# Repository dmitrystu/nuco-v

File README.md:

# NUCO-V

+ Designed for the STM32F7 and STM32H7 series
+ Pin-compatible with NUCLEO-64 boards
+ Integrated [Blackmagic probe](https://github.com/blacksphere/blackmagic)

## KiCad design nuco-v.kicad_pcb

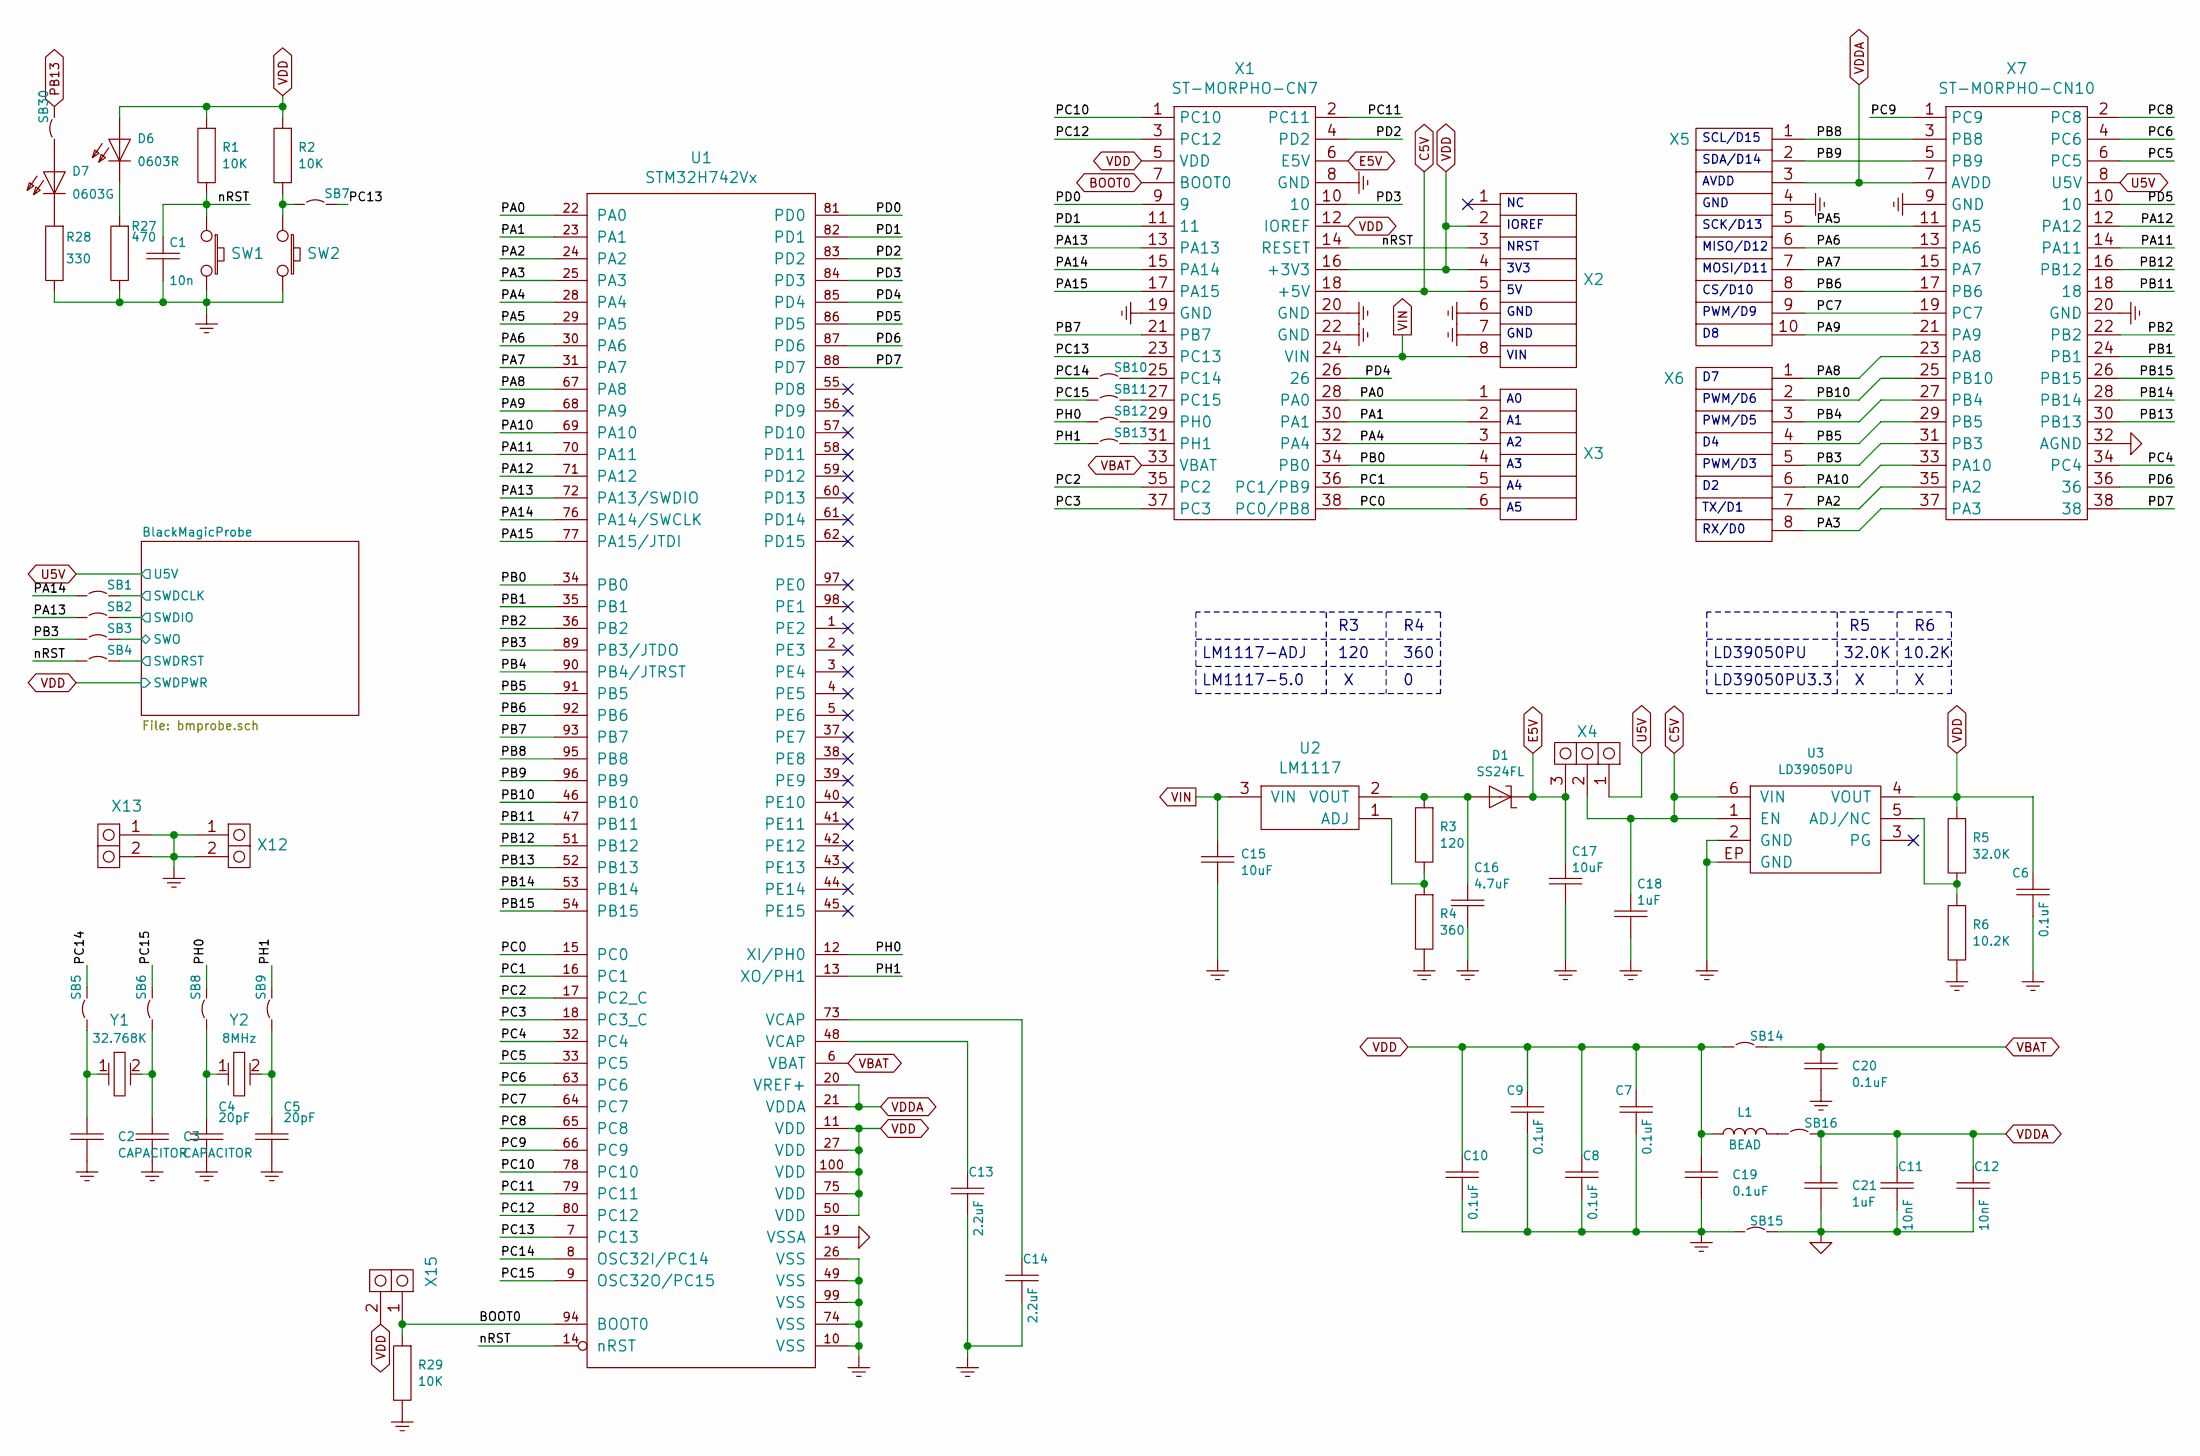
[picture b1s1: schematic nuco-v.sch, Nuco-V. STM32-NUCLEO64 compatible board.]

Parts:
C1: 10n; SMD-0603C
C2, C3: CAPACITOR; SMD-0603C
C4, C5: 20pF; SMD-0603C
C6, C7, C8, C9, C10, C19, C20: 0.1uF; SMD-0603C
C11, C12: 10nF; SMD-0603C
C13, C14: 2.2uF; SMD-0603C
C15, C17: 10uF; SMD-1206C
C16: 4.7uF; SMD-0805C
C18, C21: 1uF; SMD-0603C
D1: SS24FL; SOD-123F
D6: 0603R; LED-0603
D7: 0603G; LED-0603
L1: BEAD; SMD-0603L
R1, R2, R29: 10K; SMD-0603R
R3: 120; SMD-0603R
R4: 360; SMD-0603R
R5: 32.0K; SMD-0603R
R6: 10.2K; SMD-0603R
R27: 470; SMD-0603R
R28: 330; SMD-0603R
SB1, SB2, SB3, SB4, SB5, SB6, SB7, SB8, SB9, SB10, SB11, SB12, SB13, SB14, SB15, SB16, SB30: JUMPER; SMD-0603R
SW1, SW2: BUTTON1; B3U-1000P-B
U1: STM32H742Vx; QFPX50P140X140-100
U2: LM1117; SOT-223-3
U3: LD39050PU; DFNX95P030X030-6
X1: ST-MORPHO-CN7; DS1021-2X19S61
X2: CONN-08P1L; DS1023-1X08A
X3: CONN-06P1L; DS1025-1X06S61
X4: CONN-03P1L; DS1021-1X03S61
X5: CONN-10P1L; DS1023-1X10A
X6: CONN-08P1L; DS1021-2X04S61
X7: ST-MORPHO-CN10; DS1021-2X19S61
X12, X13: CONN-02P1LA; DS1021-1X02S61
X15: CONN-02P1L; DS1021-1X02S61
Y1: 32.768K; KX-327L
Y2: 8MHz; KX-3H

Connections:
/BlackMagicProbe/SWDCLK: SB1.2 (J2); also elsewhere on the board
/BlackMagicProbe/SWDIO: SB2.2 (J2); also elsewhere on the board
/BlackMagicProbe/SWDRST: SB4.2 (J2); also elsewhere on the board
/BlackMagicProbe/SWO: SB3.2 (J2); also elsewhere on the board
/PA0: U1.22 (PA0), X1.28 (PA0), X3.1
/PA1: U1.23 (PA1), X1.30 (PA1), X3.2
/PA2: U1.24 (PA2), X6.7, X7.35 (PA2)
/PA3: U1.25 (PA3), X6.8, X7.37 (PA3)
/PA4: U1.28 (PA4), X1.32 (PA4), X3.3
/PA5: U1.29 (PA5), X5.5, X7.11 (PA5)
/PA6: U1.30 (PA6), X5.6, X7.13 (PA6)
/PA7: U1.31 (PA7), X5.7, X7.15 (PA7)
/PA8: U1.67 (PA8), X6.1, X7.23 (PA8)
/PA9: U1.68 (PA9), X5.10, X7.21 (PA9)
/PA10: U1.69 (PA10), X6.6, X7.33 (PA10)
/PA11: U1.70 (PA11), X7.14 (PA11)
/PA12: U1.71 (PA12), X7.12 (PA12)
/PA13: SB2.1 (J1), U1.72 (PA13/SWDIO), X1.13 (PA13)
/PA14: SB1.1 (J1), U1.76 (PA14/SWCLK), X1.15 (PA14)
/PA15: U1.77 (PA15/JTDI), X1.17 (PA15)
/PB0: U1.34 (PB0), X1.34 (PB0), X3.4
/PB1: U1.35 (PB1), X7.24 (PB1)
/PB2: U1.36 (PB2), X7.22 (PB2)
/PB3: SB3.1 (J1), U1.89 (PB3/JTDO), X6.5, X7.31 (PB3)
/PB4: U1.90 (PB4/JTRST), X6.3, X7.27 (PB4)
/PB5: U1.91 (PB5), X6.4, X7.29 (PB5)
/PB6: U1.92 (PB6), X5.8, X7.17 (PB6)
/PB7: U1.93 (PB7), X1.21 (PB7)
/PB8: U1.95 (PB8), X5.1, X7.3 (PB8)
/PB9: U1.96 (PB9), X5.2, X7.5 (PB9)
/PB10: U1.46 (PB10), X6.2, X7.25 (PB10)
/PB11: U1.47 (PB11), X7.18
/PB12: U1.51 (PB12), X7.16 (PB12)
/PB14: U1.53 (PB14), X7.28 (PB14)
/PB15: U1.54 (PB15), X7.26 (PB15)
/PC0: U1.15 (PC0), X1.38 (PC0/PB8), X3.6
/PC1: U1.16 (PC1), X1.36 (PC1/PB9), X3.5
/PC2: U1.17 (PC2_C), X1.35 (PC2)
/PC3: U1.18 (PC3_C), X1.37 (PC3)
/PC4: U1.32 (PC4), X7.34 (PC4)
/PC5: U1.33 (PC5), X7.6 (PC5)
/PC6: U1.63 (PC6), X7.4 (PC6)
/PC7: U1.64 (PC7), X5.9, X7.19 (PC7)
/PC8: U1.65 (PC8), X7.2 (PC8)
/PC9: U1.66 (PC9), X7.1 (PC9)
/PC10: U1.78 (PC10), X1.1 (PC10)
/PC11: U1.79 (PC11), X1.2 (PC11)
/PC12: U1.80 (PC12), X1.3 (PC12)
/PC13: SB7.2 (J2), U1.7 (PC13), X1.23 (PC13)
/PC14: SB5.2 (J2), SB10.1 (J1), U1.8 (OSC32I/PC14)
/PC15: SB6.2 (J2), SB11.1 (J1), U1.9 (OSC32O/PC15)
/PD0: U1.81 (PD0), X1.9
/PD1: U1.82 (PD1), X1.11
/PD2: U1.83 (PD2), X1.4 (PD2)
/PD3: U1.84 (PD3), X1.10
/PD4: U1.85 (PD4), X1.26
/PD5: U1.86 (PD5), X7.10
/PD6: U1.87 (PD6), X7.36
/PD7: U1.88 (PD7), X7.38
/PH0: SB8.2 (J2), SB12.1 (J1), U1.12 (XI/PH0)
/PH1: SB9.2 (J2), SB13.1 (J1), U1.13 (XO/PH1)
/nRST: C1.1 (C1), R1.2 (R2), SB4.1 (J1), SW1.1 (CMN), U1.14 (nRST), X1.14 (RESET), X2.3
AGND: C11.2 (C2), C12.2 (C2), C21.2 (C2), SB15.2 (J2), U1.19 (VSSA), X7.32 (AGND)
BOOT0: R29.1 (R1), U1.94 (BOOT0), X1.7 (BOOT0), X15.1
C5V: C18.1 (C1), U3.1 (EN), U3.6 (VIN), X1.18 (+5V), X2.5, X4.2
E5V: C17.1 (C1), D1.1 (K), X1.6 (E5V), X4.3
unnamed: C2.1 (C1), SB5.1 (J1), Y1.1 (Q1)
unnamed: C3.1 (C1), SB6.1 (J1), Y1.2 (Q2)
unnamed: C4.1 (C1), SB8.1 (J1), Y2.1 (Q1)
unnamed: C5.1 (C1), SB9.1 (J1), Y2.2 (Q2)
unnamed: C13.1 (C1), U1.48 (VCAP)
unnamed: C14.1 (C1), U1.73 (VCAP)
unnamed: C16.1 (C1), D1.2 (A), R3.1 (R1), U2.2 (VOUT)
unnamed: D6.K, R27.1 (R1)
unnamed: D7.A, SB30.1 (J1)
unnamed: D7.K, R28.1 (R1)
unnamed: L1.2 (R2), SB16.1 (J1)
unnamed: R2.2 (R2), SB7.1 (J1), SW2.1 (CMN)
unnamed: R3.2 (R2), R4.1 (R1), U2.1 (ADJ)
unnamed: R5.2 (R2), R6.1 (R1), U3.5 (ADJ/NC)
unnamed: SB10.2 (J2), X1.25 (PC14)
unnamed: SB11.2 (J2), X1.27 (PC15)
unnamed: SB12.2 (J2), X1.29 (PH0)
unnamed: SB13.2 (J2), X1.31 (PH1)
PB13: SB30.2 (J2), U1.52 (PB13), X7.30 (PB13)
PGND: C1.2 (C2), C2.2 (C2), C3.2 (C2), C4.2 (C2), C5.2 (C2), C6.2 (C2), C7.2 (C2), C8.2 (C2), C9.2 (C2), C10.2 (C2), C13.2 (C2), C14.2 (C2), C15.2 (C2), C16.2 (C2), C17.2 (C2), C18.2 (C2), C19.2 (C2), C20.2 (C2), R4.2 (R2), R6.2 (R2), R27.2 (R2), R28.2 (R2), R29.2 (R2), SB15.1 (J1), SW1.2 (NO), SW2.2 (NO), U1.10 (VSS), U1.26 (VSS), U1.49 (VSS), U1.74 (VSS), U1.99 (VSS), U3.2 (GND), U3.EP (GND), X1.8 (GND), X1.19 (GND), X1.20 (GND), X1.22 (GND), X2.6, X2.7, X5.4, X7.9 (GND), X7.20 (GND), X12.1, X12.2, X13.1, X13.2; also elsewhere on the board
U5V: X4.1, X7.8 (U5V); also elsewhere on the board
VBAT: C20.1 (C1), SB14.2 (J2), U1.6 (VBAT), X1.33 (VBAT)
VDD: C6.1 (C1), C7.1 (C1), C8.1 (C1), C9.1 (C1), C10.1 (C1), C19.1 (C1), D6.A, L1.1 (R1), R1.1 (R1), R2.1 (R1), R5.1 (R1), SB14.1 (J1), U1.11 (VDD), U1.27 (VDD), U1.50 (VDD), U1.75 (VDD), U1.100 (VDD), U3.4 (VOUT), X1.5 (VDD), X1.12 (IOREF), X1.16 (+3V3), X2.2, X2.4, X15.2; also elsewhere on the board
VDDA: C11.1 (C1), C12.1 (C1), C21.1 (C1), SB16.2 (J2), U1.20 (VREF+), U1.21 (VDDA), X5.3, X7.7 (AVDD)
VIN: C15.1 (C1), U2.3 (VIN), X1.24 (VIN), X2.8

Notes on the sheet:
SCL/D15
SDA/D14
AVDD
GND
SCK/D13
MISO/D12
MOSI/D11
CS/D10
PWM/D9
PWM/D6
PWM/D5
PWM/D3
TX/D1
RX/D0
IOREF
NRST
3V3
VIN
LM1117-ADJ
LM1117-5.0
120
360
LD39050PU
LD39050PU3.3
10.2K
32.0K

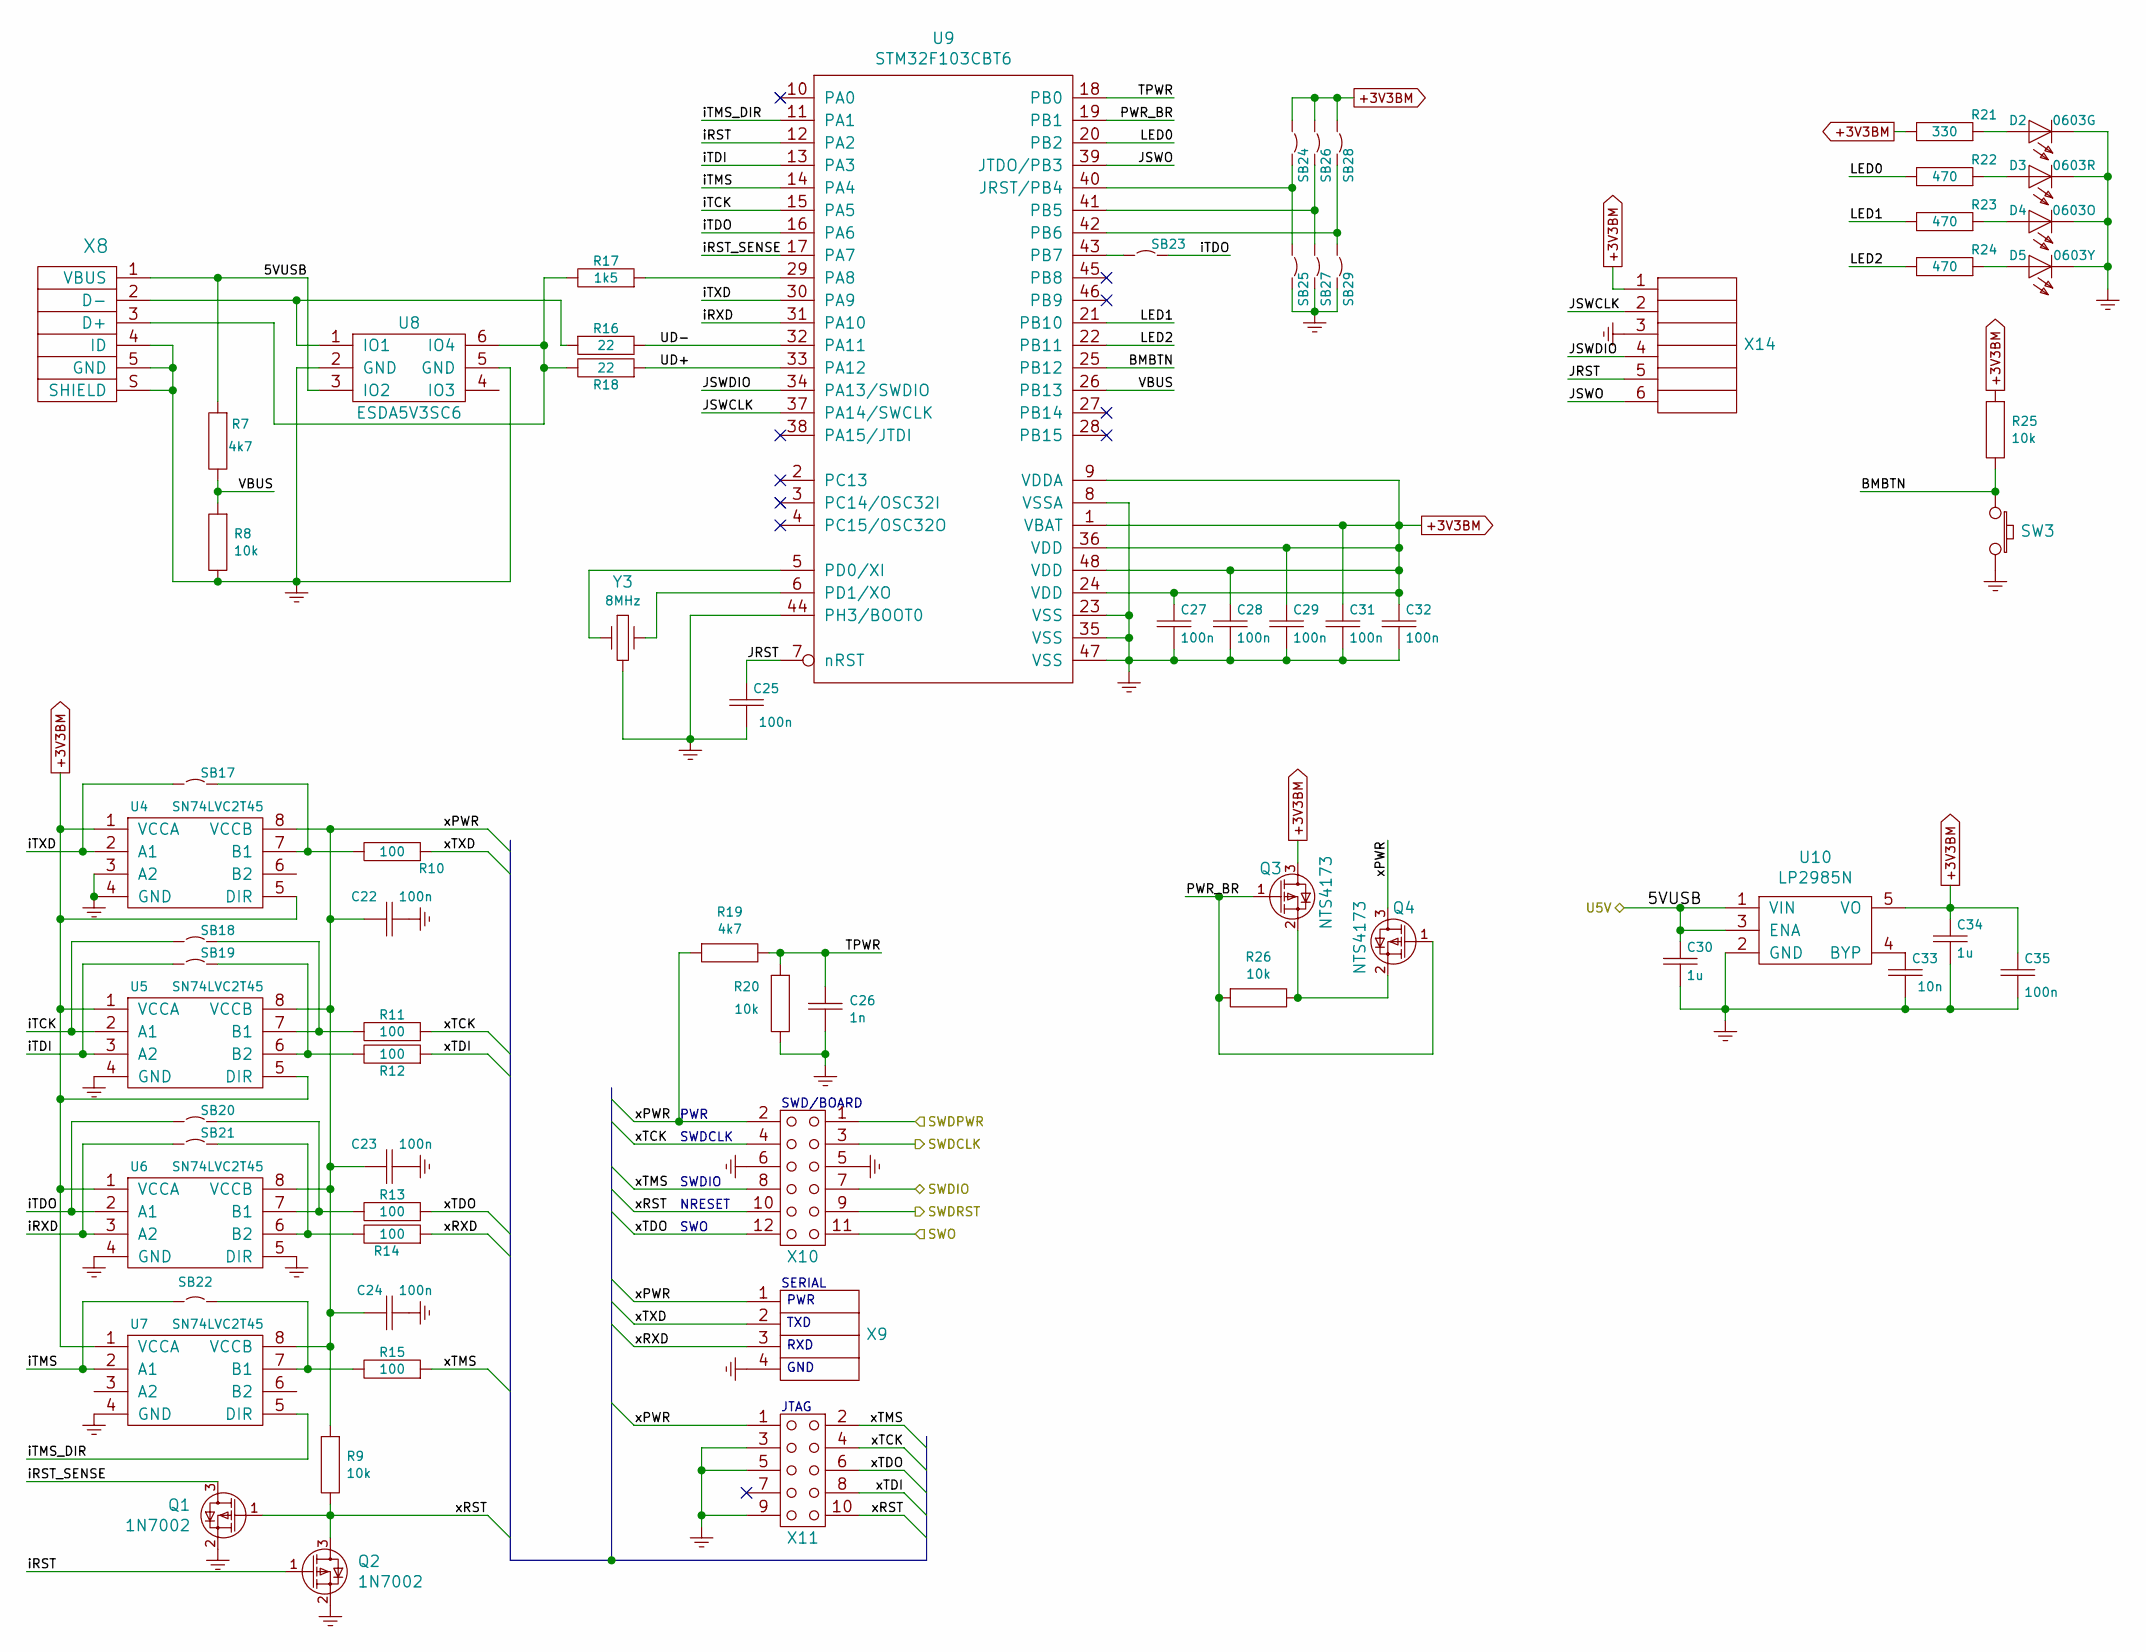
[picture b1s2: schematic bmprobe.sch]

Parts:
C22, C23, C24, C25, C27, C28, C29, C31, C32, C35: 100n; SMD-0603C
C26: 1n; SMD-0603C
C30, C34: 1u; SMD-0603C
C33: 10n; SMD-0603C
D2: 0603G; LED-0603
D3: 0603R; LED-0603
D4: 0603O; LED-0603
D5: 0603Y; LED-0603
Q1, Q2: 1N7002; SC-70-3
Q3, Q4: NTS4173; SC-70-3
R7, R19: 4k7; SMD-0603R
R8, R9, R20, R25, R26: 10k; SMD-0603R
R10, R11, R12, R13, R14, R15: 100; SMD-0603R
R16, R18: 22; SMD-0603R
R17: 1k5; SMD-0603R
R21: 330; SMD-0603R
R22, R23, R24: 470; SMD-0603R
SB17, SB18, SB19, SB20, SB21, SB22, SB23, SB24, SB25, SB26, SB27, SB28, SB29: JUMPER; SMD-0603R
SW3: BUTTON1; B3U-1000P-B
U4, U5, U6, U7: SN74LVC2T45; SO65P030X030-8
U8: ESDA5V3SC6; SOT-23-6
U9: STM32F103CBT6; QFP50P070X070-48
U10: LP2985N; SOT-23-5
X8: USB-OTG; AMP10118194-0001LF
X9: CONN-04P1L; DS1021-1X04S61
X10: CONN-12P2L; DS1021-2X06S61
X11: CONN-10P2L; DS1031-08-2X05P8BSX
X14: CONN-06P1L; DS1023-1X06A
Y3: 8MHz; MUR-CSTCE

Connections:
+3V3BM: C27.1 (C1), C28.1 (C1), C29.1 (C1), C31.1 (C1), C32.1 (C1), C34.1 (C1), C35.1 (C1), Q3.3 (D), R21.2 (R2), R25.1 (R1), SB24.1 (J1), SB26.1 (J1), SB28.1 (J1), U4.1 (VCCA), U4.5 (DIR), U5.1 (VCCA), U5.5 (DIR), U6.1 (VCCA), U7.1 (VCCA), U9.1 (VBAT), U9.9 (VDDA), U9.24 (VDD), U9.36 (VDD), U9.48 (VDD), U10.5 (VO), X14.1
/BlackMagicProbe/BMBTN: R25.2 (R2), SW3.1 (CMN), U9.25 (PB12)
/BlackMagicProbe/JRST: C25.1 (C1), U9.7 (nRST), X14.5
/BlackMagicProbe/JSWCLK: U9.37 (PA14/SWCLK), X14.2
/BlackMagicProbe/JSWDIO: U9.34 (PA13/SWDIO), X14.4
/BlackMagicProbe/JSWO: U9.39 (JTDO/PB3), X14.6
/BlackMagicProbe/LED0: R22.2 (R2), U9.20 (PB2)
/BlackMagicProbe/LED1: R23.2 (R2), U9.21 (PB10)
/BlackMagicProbe/LED2: R24.2 (R2), U9.22 (PB11)
/BlackMagicProbe/PWR_BR: Q3.1 (G), Q4.1 (G), R26.1 (R1), U9.19 (PB1)
/BlackMagicProbe/SWDCLK: X10.3; also elsewhere on the board
/BlackMagicProbe/SWDIO: X10.7; also elsewhere on the board
/BlackMagicProbe/SWDRST: X10.9; also elsewhere on the board
/BlackMagicProbe/SWO: X10.11; also elsewhere on the board
/BlackMagicProbe/TPWR: C26.1 (C1), R19.2 (R2), R20.1 (R1), U9.18 (PB0)
/BlackMagicProbe/UD+: R18.1 (R1), U9.33 (PA12)
/BlackMagicProbe/UD-: R16.2 (R2), U9.32 (PA11)
/BlackMagicProbe/VBUS: R7.2 (R2), R8.1 (R1), U9.26 (PB13)
/BlackMagicProbe/iRST: Q2.1 (G), U9.12 (PA2)
/BlackMagicProbe/iRST_SENSE: Q1.3 (D), U9.17 (PA7)
/BlackMagicProbe/iRXD: SB21.1 (J1), U6.3 (A2), U9.31 (PA10)
/BlackMagicProbe/iTCK: SB18.1 (J1), U5.2 (A1), U9.15 (PA5)
/BlackMagicProbe/iTDI: SB19.1 (J1), U5.3 (A2), U9.13 (PA3)
/BlackMagicProbe/iTDO: SB20.1 (J1), SB23.2 (J2), U6.2 (A1), U9.16 (PA6)
/BlackMagicProbe/iTMS: SB22.1 (J1), U7.2 (A1), U9.14 (PA4)
/BlackMagicProbe/iTMS_DIR: U7.5 (DIR), U9.11 (PA1)
/BlackMagicProbe/iTXD: SB17.1 (J1), U4.2 (A1), U9.30 (PA9)
/BlackMagicProbe/xPWR: C22.2 (C2), C23.2 (C2), C24.2 (C2), Q4.3 (D), R9.1 (R1), R19.1 (R1), U4.8 (VCCB), U5.8 (VCCB), U6.8 (VCCB), U7.8 (VCCB), X9.1, X10.2, X11.1
/BlackMagicProbe/xRST: Q1.1 (G), Q2.3 (D), R9.2 (R2), X10.10, X11.10
/BlackMagicProbe/xRXD: R14.1 (R1), X9.3
/BlackMagicProbe/xTCK: R11.1 (R1), X10.4, X11.4
/BlackMagicProbe/xTDI: R12.1 (R1), X11.8
/BlackMagicProbe/xTDO: R13.1 (R1), X10.12, X11.6
/BlackMagicProbe/xTMS: R15.1 (R1), X10.8, X11.2
/BlackMagicProbe/xTXD: R10.1 (R1), X9.2
unnamed: C33.1 (C1), U10.4 (BYP)
unnamed: D2.A, R21.1 (R1)
unnamed: D3.A, R22.1 (R1)
unnamed: D4.A, R23.1 (R1)
unnamed: D5.A, R24.1 (R1)
unnamed: Q3.2 (S), Q4.2 (S), R26.2 (R2)
unnamed: R10.2 (R2), SB17.2 (J2), U4.7 (B1)
unnamed: R11.2 (R2), SB18.2 (J2), U5.7 (B1)
unnamed: R12.2 (R2), SB19.2 (J2), U5.6 (B2)
unnamed: R13.2 (R2), SB20.2 (J2), U6.7 (B1)
unnamed: R14.2 (R2), SB21.2 (J2), U6.6 (B2)
unnamed: R15.2 (R2), SB22.2 (J2), U7.7 (B1)
unnamed: R16.1 (R1), U8.1 (IO1), X8.2 (D-)
unnamed: R17.1 (R1), U9.29 (PA8)
unnamed: R17.2 (R2), R18.2 (R2), U8.6 (IO4), X8.3 (D+)
unnamed: SB23.1 (J1), U9.43 (PB7)
unnamed: SB24.2 (J2), SB25.1 (J1), U9.40 (JRST/PB4)
unnamed: SB26.2 (J2), SB27.1 (J1), U9.41 (PB5)
unnamed: SB28.2 (J2), SB29.1 (J1), U9.42 (PB6)
unnamed: U9.5 (PD0/XI), Y3.1 (Q1)
unnamed: U9.6 (PD1/XO), Y3.3 (Q2)
PGND: C22.1 (C1), C23.1 (C1), C24.1 (C1), C25.2 (C2), C26.2 (C2), C27.2 (C2), C28.2 (C2), C29.2 (C2), C30.2 (C2), C31.2 (C2), C32.2 (C2), C33.2 (C2), C34.2 (C2), C35.2 (C2), D2.K, D3.K, D4.K, D5.K, Q1.2 (S), Q2.2 (S), R8.2 (R2), R20.2 (R2), SB25.2 (J2), SB27.2 (J2), SB29.2 (J2), SW3.2 (NO), U4.3 (A2), U4.4 (GND), U5.4 (GND), U6.4 (GND), U6.5 (DIR), U7.4 (GND), U8.2 (GND), U8.5 (GND), U9.8 (VSSA), U9.23 (VSS), U9.35 (VSS), U9.44 (PH3/BOOT0), U9.47 (VSS), U10.2 (GND), X8.4 (ID), X8.5 (GND), X8.S (SHIELD), X9.4, X10.5, X10.6, X11.3, X11.5, X11.9, X14.3, Y3.2 (CMN); also elsewhere on the board
U5V: C30.1 (C1), R7.1 (R1), U8.3 (IO2), U10.1 (VIN), U10.3 (ENA), X8.1 (VBUS); also elsewhere on the board
VDD: X10.1; also elsewhere on the board

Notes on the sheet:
PWR
GND
TXD
RXD
SERIAL
SWO
NRESET
SWDIO
SWDCLK
SWD/BOARD
JTAG

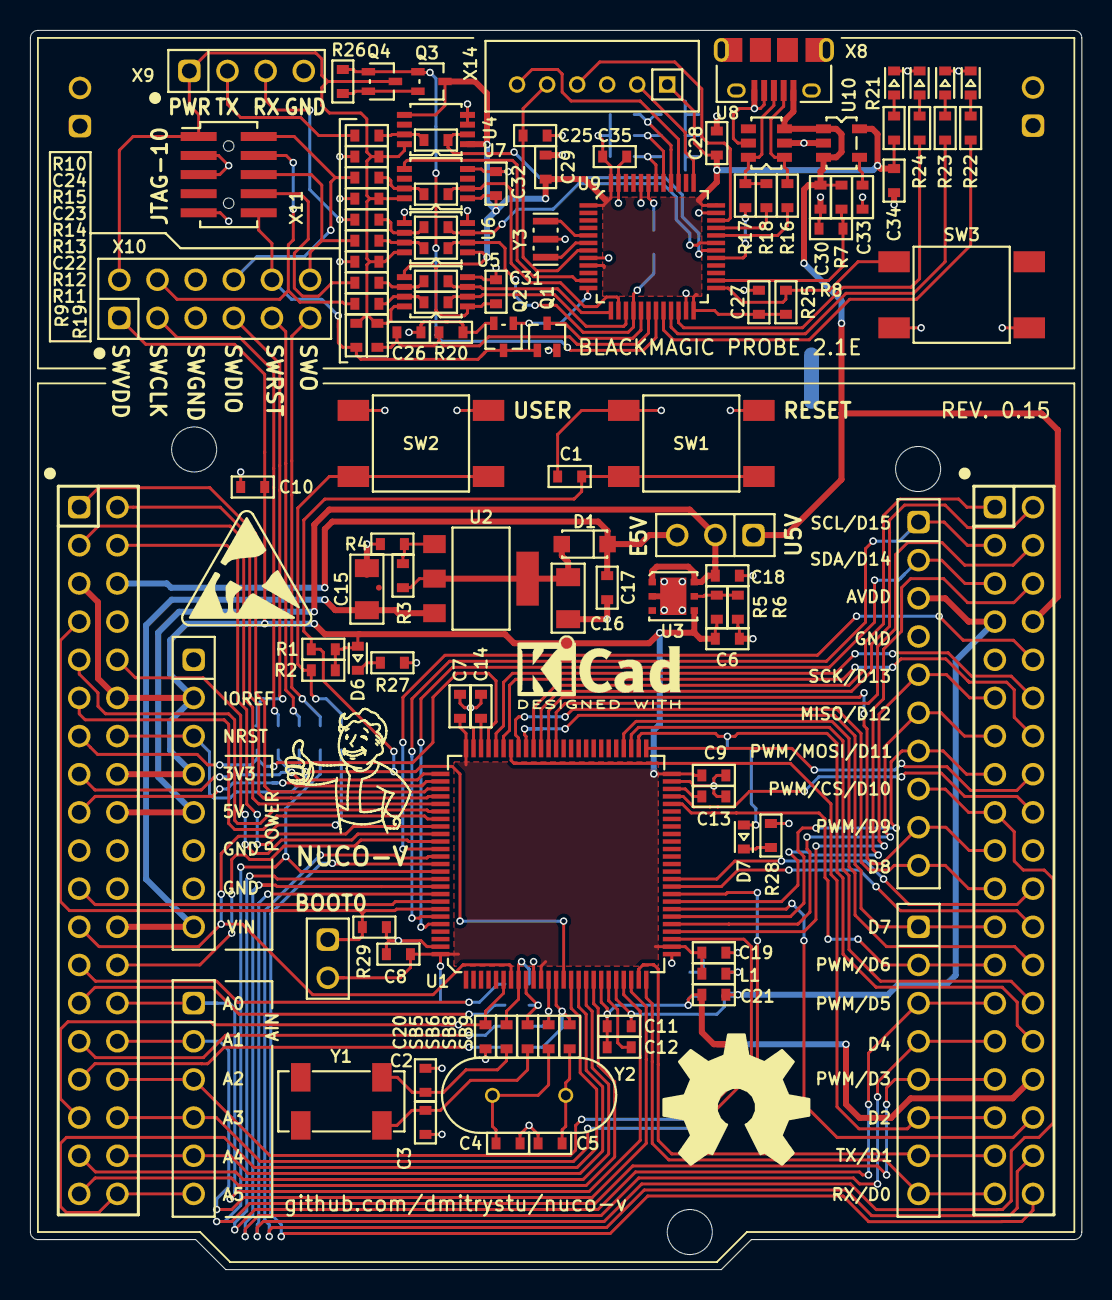
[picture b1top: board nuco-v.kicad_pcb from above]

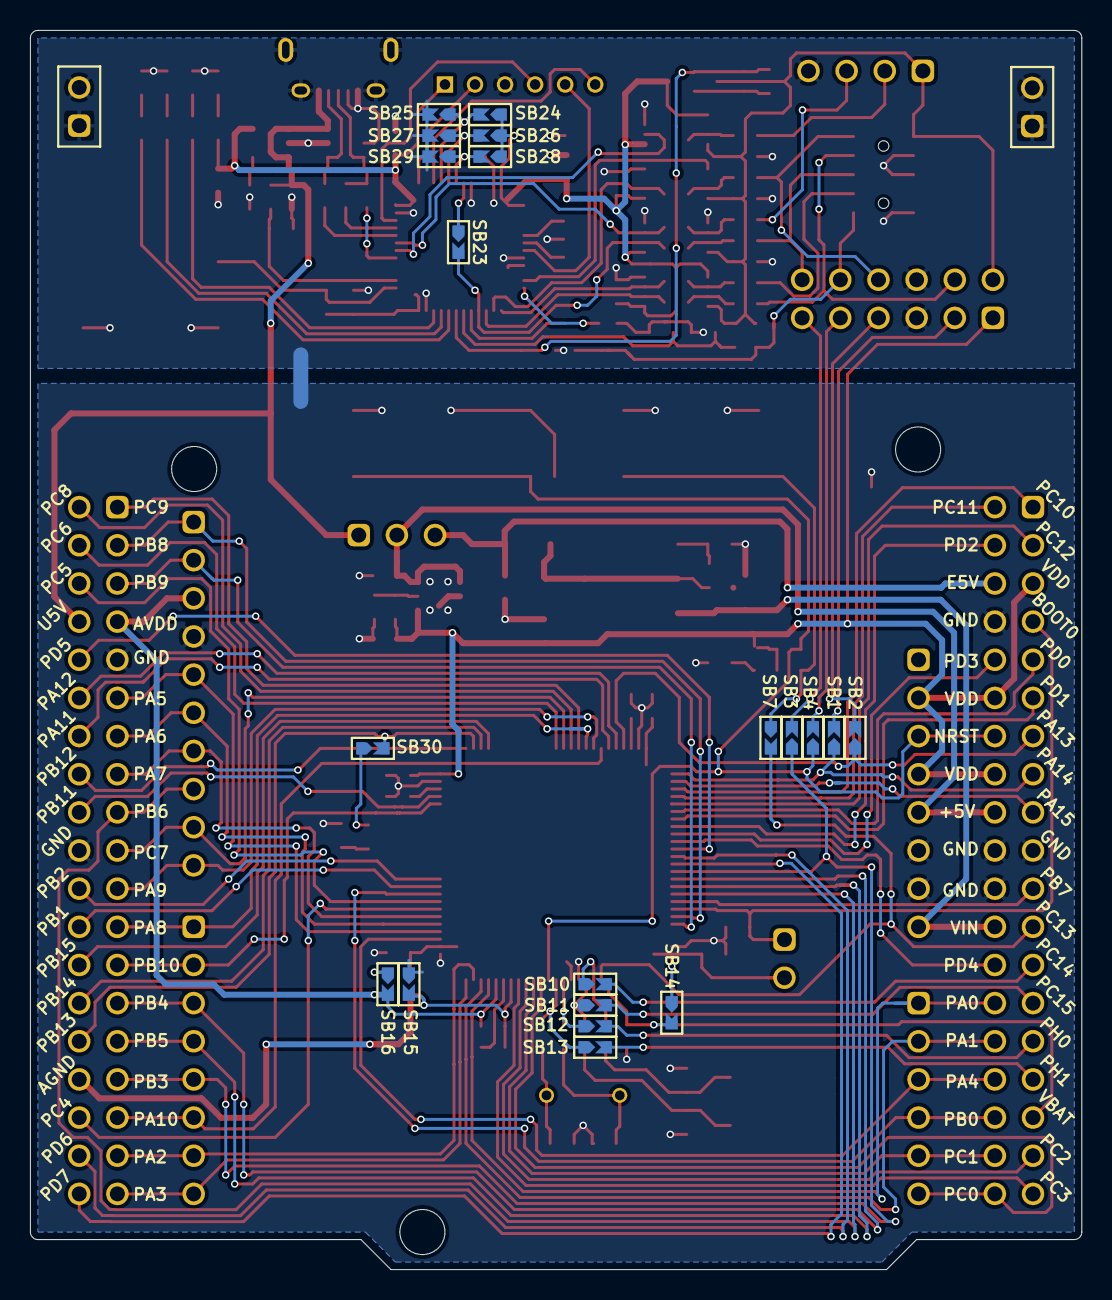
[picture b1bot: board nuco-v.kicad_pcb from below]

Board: 2 copper layers, 70.0 x 82.5 mm, 139 parts (22 on the bottom side), 143 nets.

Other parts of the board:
OSHW_FS_10MM: VAL**; OSHW_FS_10MM
svg2mod: G***; FALLOUT_1

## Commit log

2020-11-26 Initial
2021-02-03 add cache library
